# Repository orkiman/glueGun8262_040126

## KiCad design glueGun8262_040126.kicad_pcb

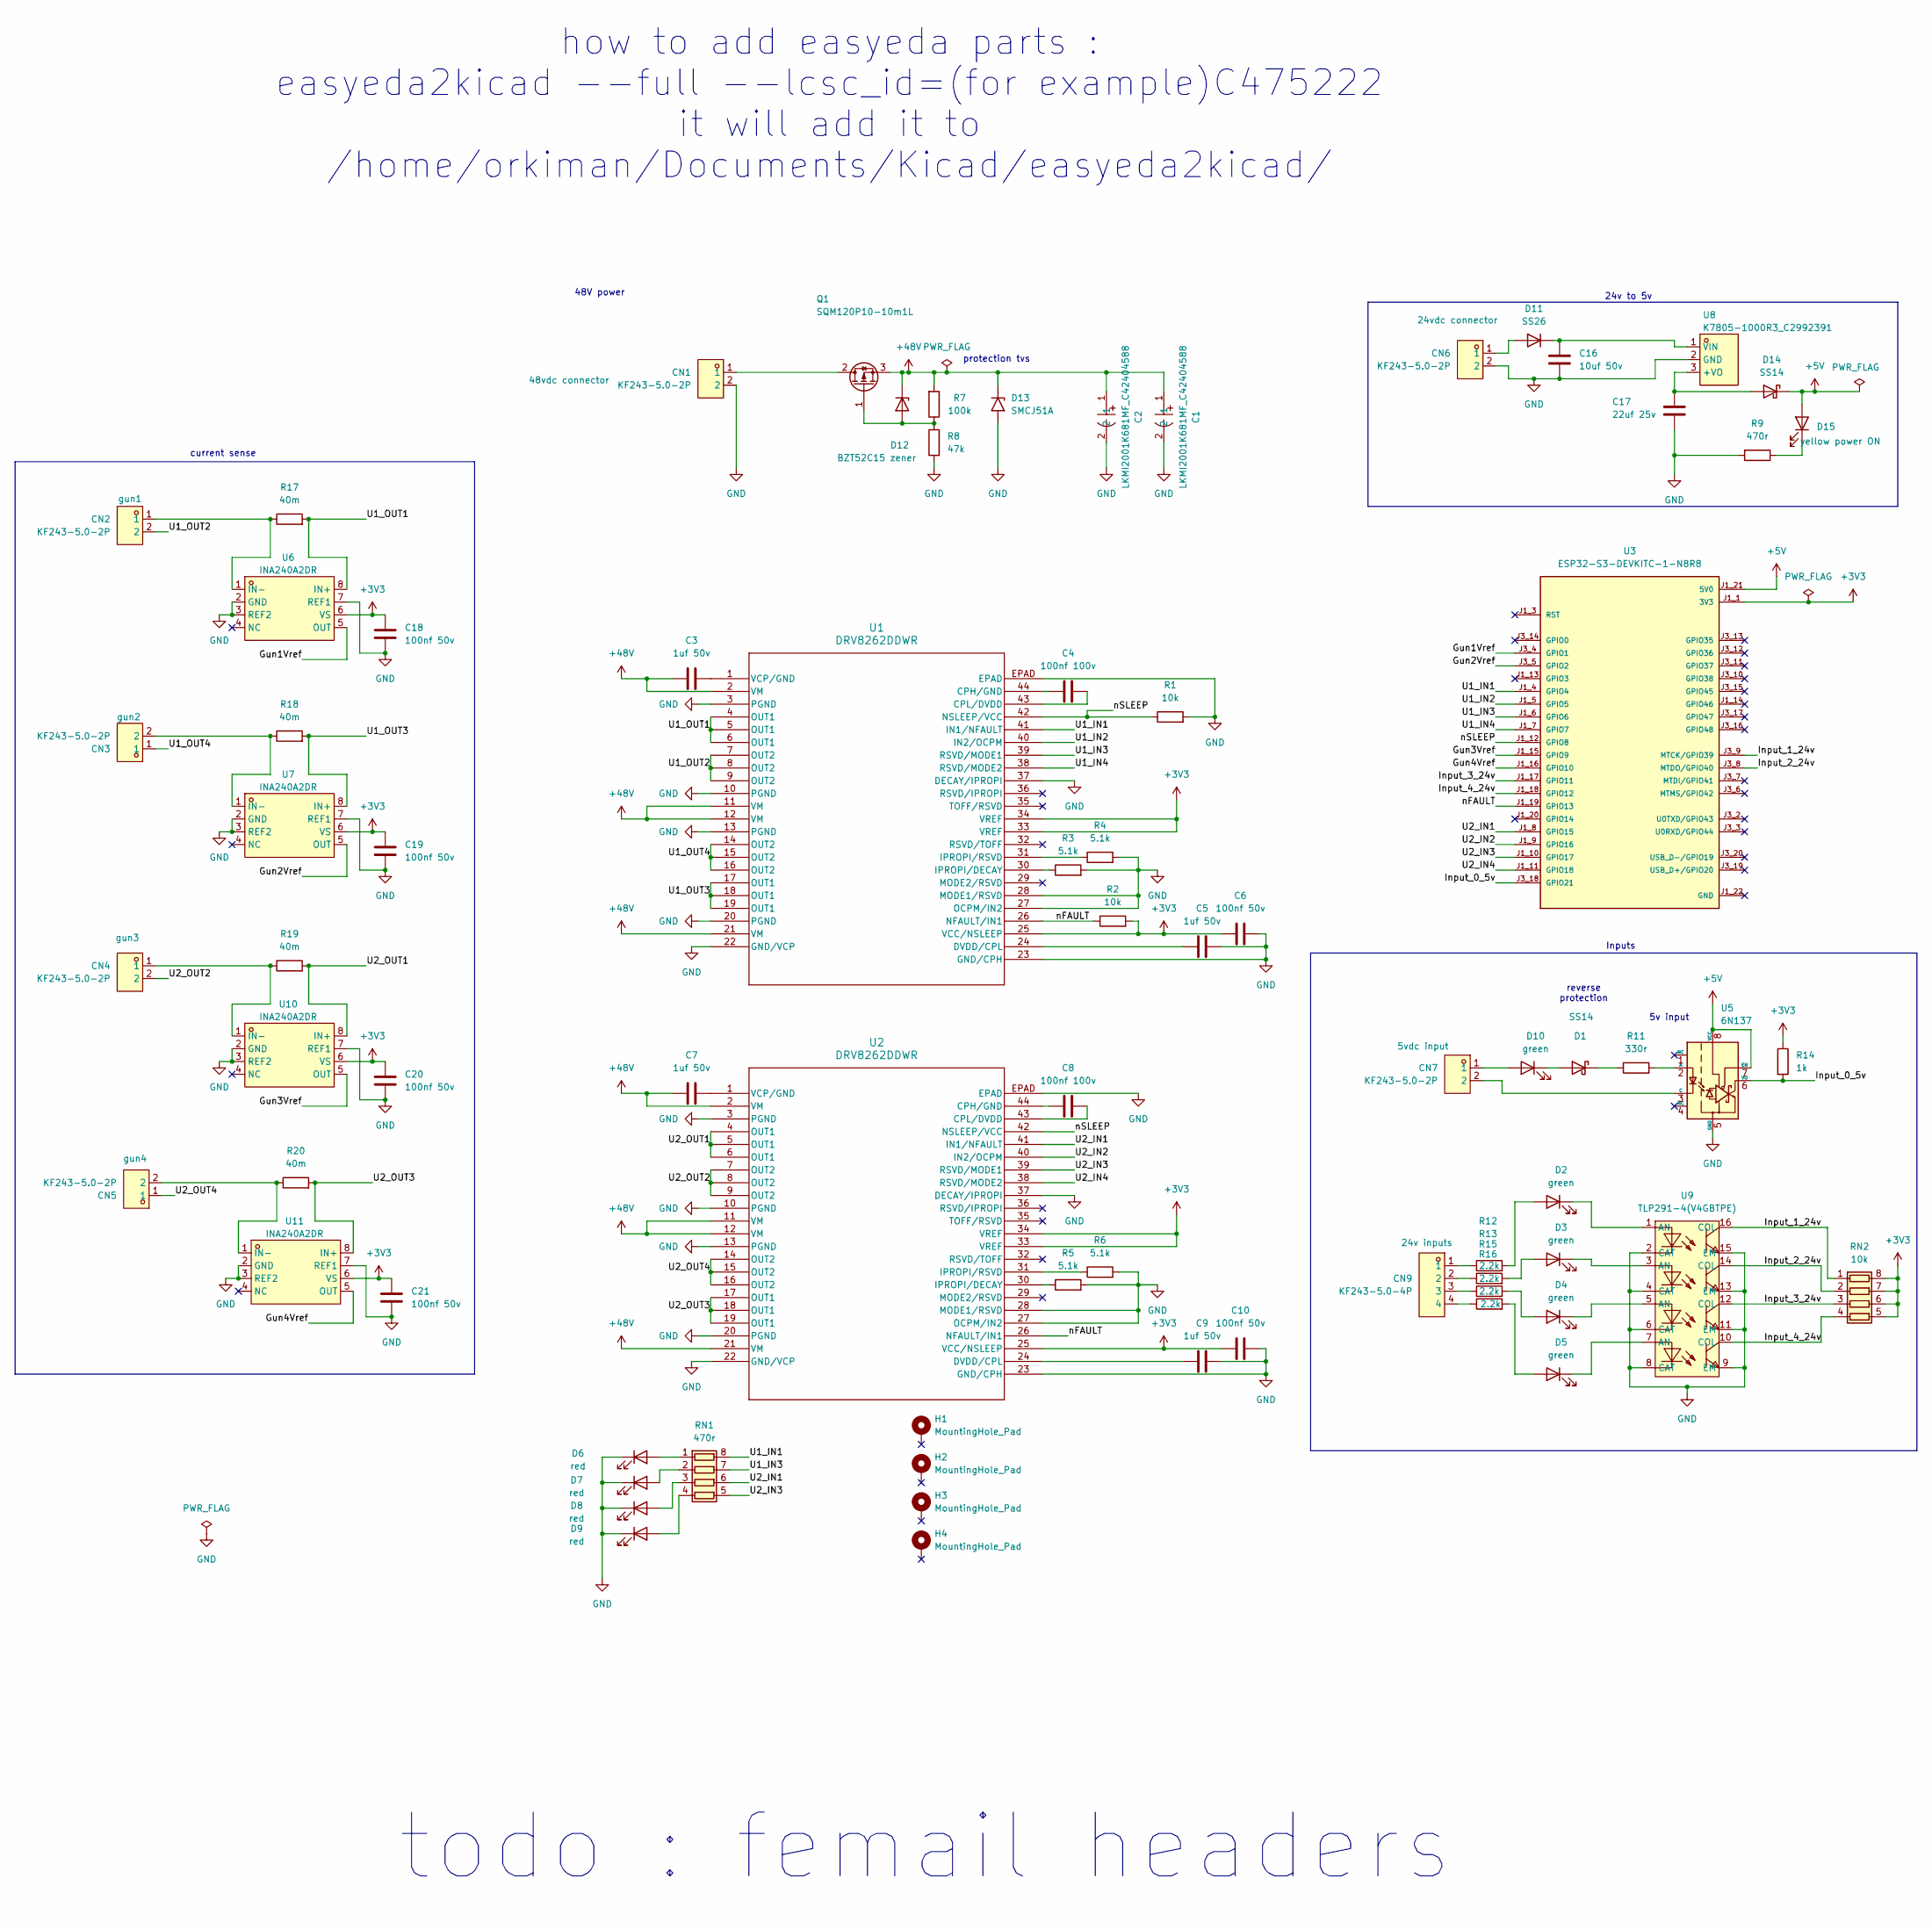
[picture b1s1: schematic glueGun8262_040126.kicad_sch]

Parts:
C1, C2: LKMI2001K681MF_C42404588; CAP-TH_BD16.0-P7.50-D0.8-FD; LCSC part C42404588
C3, C5, C7, C9: 1uf 50v; C_0603_1608Metric; lcsc C106248
C4, C8: 100nf 100v; C_0805_2012Metric; lcsc C113803
C6, C10: 100nf 50v; C_0603_1608Metric; lcsc C309458
C16: 10uf 50v; C_1206_3216Metric; lcsc C513774
C17: 22uf 25v; C_1206_3216Metric; lcsc C513771
C18, C19, C20, C21: 100nf 50v; C_0603_1608Metric; LCSC part C14663
CN1, CN2, CN3, CN4, CN5, CN6, CN7: KF243-5.0-2P; CONN-TH_P5.00_KF243-5.0-2P; LCSC part C475222
CN9: KF243-5.0-4P; CONN-TH_4P-P5.00_KF243-5.0-4P; LCSC part C475224
D1: SS14; D_SMA; part ss14; LCSC part C2480
D2, D3, D4, D5, D10: green; LED_0805_2012Metric; lcsc C2297
D6, D7, D8, D9: red; LED_0805_2012Metric; LCSC part C84256
D11: SS26; D_SMA; part ss26; LCSC part C14238
D12: BZT52C15 zener; D_SOD-123; LCSC part C2104
D13: SMCJ51A; D_SMC; LCSC part C438115
D14: SS14; D_SMA; LCSC part C2480
D15: yellow power ON; LED_0805_2012Metric; lcsc C2297
H1, H2, H3, H4: MountingHole_Pad; MountingHole_3.2mm_M3_Pad
Q1: SQM120P10-10m1L; TO-263-2; LCSC part C3281565
R1, R2: 10k; R_0603_1608Metric; lcsc C84376
R3, R4, R5, R6: 5.1k; R_0603_1608Metric; LCSC part C23186
R7: 100k; R_0805_2012Metric; LCSC part C25611
R8: 47k; R_0805_2012Metric; LCSC part C17713
R9: 470r; R_0603_1608Metric; LCSC part C23179
R11: 330r; R_0603_1608Metric; LCSC part C23138
R12, R13, R15, R16: 2.2k; R_1206_3216Metric; LCSC part C17948
R14: 1k; R_0603_1608Metric; LCSC part C21190
R17, R18, R19, R20: 40m; R_2512_6332Metric; lcsc C500722
RN1: 470r; R_Array_Convex_4x0603; LCSC part C354986
RN2: 10k; R_Array_Convex_4x0603; LCSC part C107374
U1, U2: DRV8262DDWR; HTSSOP44-DDW_TEX
U3: ESP32-S3-DEVKITC-1-N8R8; XCVR_ESP32-S3-DEVKITC-1-N8R2; PARTREV V1
U5: 6N137; SMDIP-8_W9.53mm; LCSC part C16496
U6, U7, U10, U11: INA240A2DR; SOIC-8_L4.9-W3.9-P1.27-LS6.0-BL; LCSC part C2060768
U8: K7805-1000R3_C2992391; PWRM-TH_YLPTEC_K78XX-1000R3; LCSC part C2992391
U9: TLP291-4(V4GBTPE); SOP-16_L10.3-W4.4-P1.27-LS7.0-BL; LCSC part C2848503

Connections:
+3V3: C6.1, C10.1, C18.1, C19.1, C20.1, C21.1, R2.2, R14.1, RN2.5 (R4.2), RN2.6 (R3.2), RN2.7 (R2.2), RN2.8 (R1.2), U1.25 (VCC/NSLEEP), U1.33 (VREF), U1.34 (VREF), U2.25 (VCC/NSLEEP), U2.33 (VREF), U2.34 (VREF), U3.J1_1 (3V3), U3.J1_2 (3V3), U6.6 (VS), U7.6 (VS), U10.6 (VS), U11.6 (VS)
+5V: D14.1 (K), D15.2 (A), U3.J1_21 (5V0), U5.7 (EN), U5.8 (VCC)
+48V: C1.1, C2.1, C3.1, C7.1, D12.1 (K), D13.1 (A1), Q1.3 (S), R7.2, U1.2 (VM), U1.11 (VM), U1.12 (VM), U1.21 (VM), U2.2 (VM), U2.11 (VM), U2.12 (VM), U2.21 (VM)
/Gun1Vref: U3.J3_4 (GPIO1), U6.5 (OUT)
/Gun2Vref: U3.J3_5 (GPIO2), U7.5 (OUT)
/Gun3Vref: U3.J1_15 (GPIO9), U10.5 (OUT)
/Gun4Vref: U3.J1_16 (GPIO10), U11.5 (OUT)
/Input_0_5v: R14.2, U3.J3_18 (GPIO21), U5.6 (VO)
/Input_1_24v: RN2.1 (R1.1), U3.J3_9 (MTCK/GPIO39), U9.16 (COL)
/Input_2_24v: RN2.2 (R2.1), U3.J3_8 (MTDO/GPIO40), U9.14 (COL)
/Input_3_24v: RN2.3 (R3.1), U3.J1_17 (GPIO11), U9.12 (COL)
/Input_4_24v: RN2.4 (R4.1), U3.J1_18 (GPIO12), U9.10 (COL)
/U1_IN1: RN1.8 (R1.2), U1.41 (IN1/NFAULT), U3.J1_4 (GPIO4)
/U1_IN2: U1.40 (IN2/OCPM), U3.J1_5 (GPIO5)
/U1_IN3: RN1.7 (R2.2), U1.39 (RSVD/MODE1), U3.J1_6 (GPIO6)
/U1_IN4: U1.38 (RSVD/MODE2), U3.J1_7 (GPIO7)
/U1_OUT1: R17.2, U1.4 (OUT1), U1.5 (OUT1), U1.6 (OUT1), U6.8 (IN+)
/U1_OUT2: CN2.2, U1.7 (OUT2), U1.8 (OUT2), U1.9 (OUT2)
/U1_OUT3: R18.2, U1.17 (OUT1), U1.18 (OUT1), U1.19 (OUT1), U7.8 (IN+)
/U1_OUT4: CN3.1, U1.14 (OUT2), U1.15 (OUT2), U1.16 (OUT2)
/U2_IN1: RN1.6 (R3.2), U2.41 (IN1/NFAULT), U3.J1_8 (GPIO15)
/U2_IN2: U2.40 (IN2/OCPM), U3.J1_9 (GPIO16)
/U2_IN3: RN1.5 (R4.2), U2.39 (RSVD/MODE1), U3.J1_10 (GPIO17)
/U2_IN4: U2.38 (RSVD/MODE2), U3.J1_11 (GPIO18)
/U2_OUT1: R19.2, U2.4 (OUT1), U2.5 (OUT1), U2.6 (OUT1), U10.8 (IN+)
/U2_OUT2: CN4.2, U2.7 (OUT2), U2.8 (OUT2), U2.9 (OUT2)
/U2_OUT3: R20.2, U2.17 (OUT1), U2.18 (OUT1), U2.19 (OUT1), U11.8 (IN+)
/U2_OUT4: CN5.1, U2.14 (OUT2), U2.15 (OUT2), U2.16 (OUT2)
/nFAULT: R2.1, U1.26 (NFAULT/IN1), U2.26 (NFAULT/IN1), U3.J1_19 (GPIO13)
/nSLEEP: R1.1, U1.42 (NSLEEP/VCC), U2.42 (NSLEEP/VCC), U3.J1_12 (GPIO8)
unnamed: CN9.1, R12.1
unnamed: CN9.2, R13.1
unnamed: CN9.3, R15.1
unnamed: CN9.4, R16.1
unnamed: D1.2 (A), D10.1 (K)
unnamed: D1.1 (K), R11.1
unnamed: D2.2 (A), R12.2
unnamed: D2.1 (K), U9.1 (AN)
unnamed: D3.2 (A), R13.2
unnamed: D3.1 (K), U9.3 (AN)
unnamed: D4.2 (A), R15.2
unnamed: D4.1 (K), U9.5 (AN)
unnamed: D5.2 (A), R16.2
unnamed: D5.1 (K), U9.7 (AN)
unnamed: D6.2 (A), RN1.1 (R1.1)
unnamed: D7.2 (A), RN1.2 (R2.1)
unnamed: D8.2 (A), RN1.3 (R3.1)
unnamed: D9.2 (A), RN1.4 (R4.1)
unnamed: CN7.1, D10.2 (A)
unnamed: CN6.1, D11.2 (A)
unnamed: C16.1, D11.1 (K), U8.1 (VIN)
unnamed: D12.2 (A), Q1.1 (G), R7.1, R8.2
unnamed: C17.1, D14.2 (A), U8.3 (+VO)
unnamed: D15.1 (K), R9.1
unnamed: CN1.1, Q1.2 (D)
unnamed: C4.1, U1.44 (CPH/GND)
unnamed: C4.2, U1.43 (CPL/DVDD)
unnamed: C5.1, U1.24 (DVDD/CPL)
unnamed: R3.1, U1.30 (IPROPI/DECAY)
unnamed: R4.1, U1.31 (IPROPI/RSVD)
unnamed: C3.2, U1.1 (VCP/GND)
unnamed: C8.1, U2.44 (CPH/GND)
unnamed: C8.2, U2.43 (CPL/DVDD)
unnamed: C9.1, U2.24 (DVDD/CPL)
unnamed: R5.1, U2.30 (IPROPI/DECAY)
unnamed: R6.1, U2.31 (IPROPI/RSVD)
unnamed: C7.2, U2.1 (VCP/GND)
unnamed: R11.2, U5.2 (A)
unnamed: CN7.2, U5.3 (C)
unnamed: CN2.1, R17.1, U6.1 (IN-)
unnamed: CN3.2, R18.1, U7.1 (IN-)
unnamed: CN4.1, R19.1, U10.1 (IN-)
unnamed: CN5.2, R20.1, U11.1 (IN-)

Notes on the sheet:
48V power
Inputs
todo : femail headers
reverse protection
how to add easyeda parts : easyeda2kicad --full --lcsc_id=(for example)C475222 it will add it to /home/orkiman/Documents/Kicad/easyeda2kicad/
24v to 5v
current sense
5v input
protection tvs

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
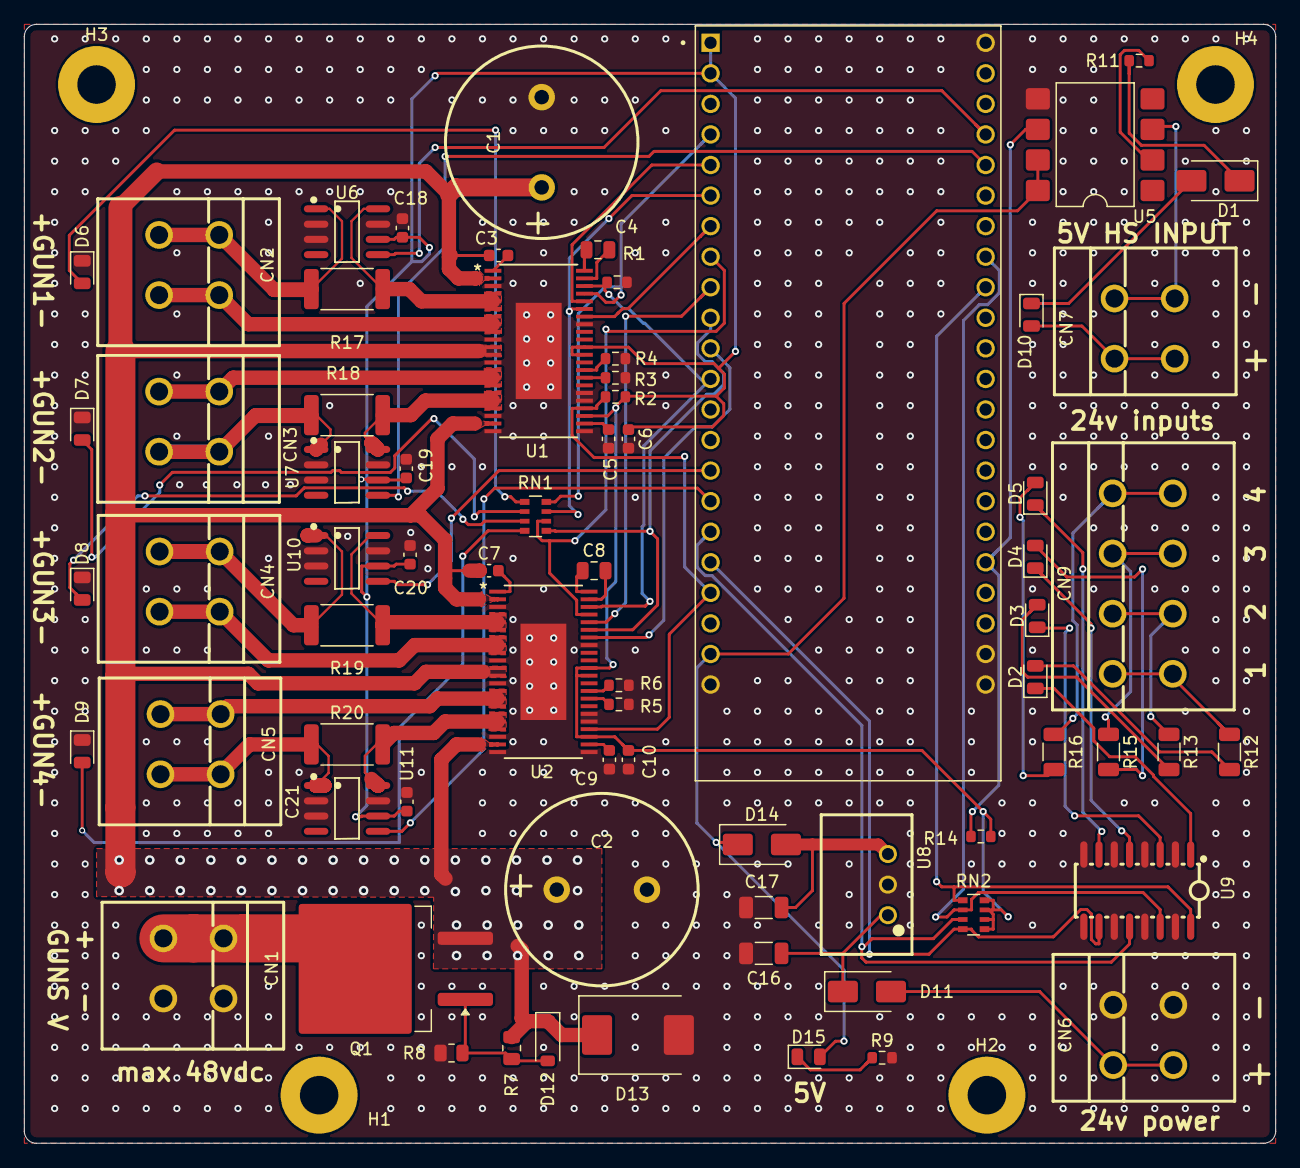
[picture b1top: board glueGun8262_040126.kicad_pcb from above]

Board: 2 copper layers, 104.0 x 93.0 mm, 75 parts (0 on the bottom side), 74 nets.

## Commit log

2026-01-04 Initial commit: ESP32-S3 and DRV8262 project setup
2026-01-09 ina240 schunts in series with sol
2026-01-11 satrted laying pcb
2026-01-12 cont
2026-01-12 cont arranging board. and easyeda models now in project folder
2026-01-12 with 3d files
2026-01-13 in the process of changing 0402 to 0603 footprints
2026-01-14 cont rearrange pcb
2026-01-17 high power routed and locked
2026-01-18 no drc errors1
2026-01-18 no drcErrors2 before replacing U5 to smt
2026-01-20 added mounting holes
2026-01-21 no drc errors with mounting holes
2026-01-25 add protection schotoky diode to 5v supply
2026-01-26 saved
2026-02-05 schematics updated pinout
2026-02-08 pcb rewired new pinout
2026-02-08 no drc errors
2026-02-26 Ignore KiCad autosave file
2026-02-28 redesigned before freerouting
2026-02-28 routed-check
2026-03-03 minor mounting hole position mostly git test
2026-03-03 minor relocation
2026-03-03 test
2026-03-05 redesign rectanglular board routed no errors
2026-03-05 bulk cap rotated
2026-03-05 cap place correction
2026-03-07 dont remember
2026-03-07 footprintes updated for home desktop
2026-03-07 leds position at the correct locations
2026-03-07 start to assign footprints
2026-03-07 almost done find lcsc parts
2026-03-08 before adding headers
2026-03-08 design done
2026-03-08 incresed 48v clearance to 0.3
2026-03-08 Clean up autosave files and sync project
2026-03-11 Update .gitignore for KiCad 9 and UI settings
2026-04-05 Add Linux/Editor temp files to ignore
2026-04-05 Ignore escaped auto-save files
